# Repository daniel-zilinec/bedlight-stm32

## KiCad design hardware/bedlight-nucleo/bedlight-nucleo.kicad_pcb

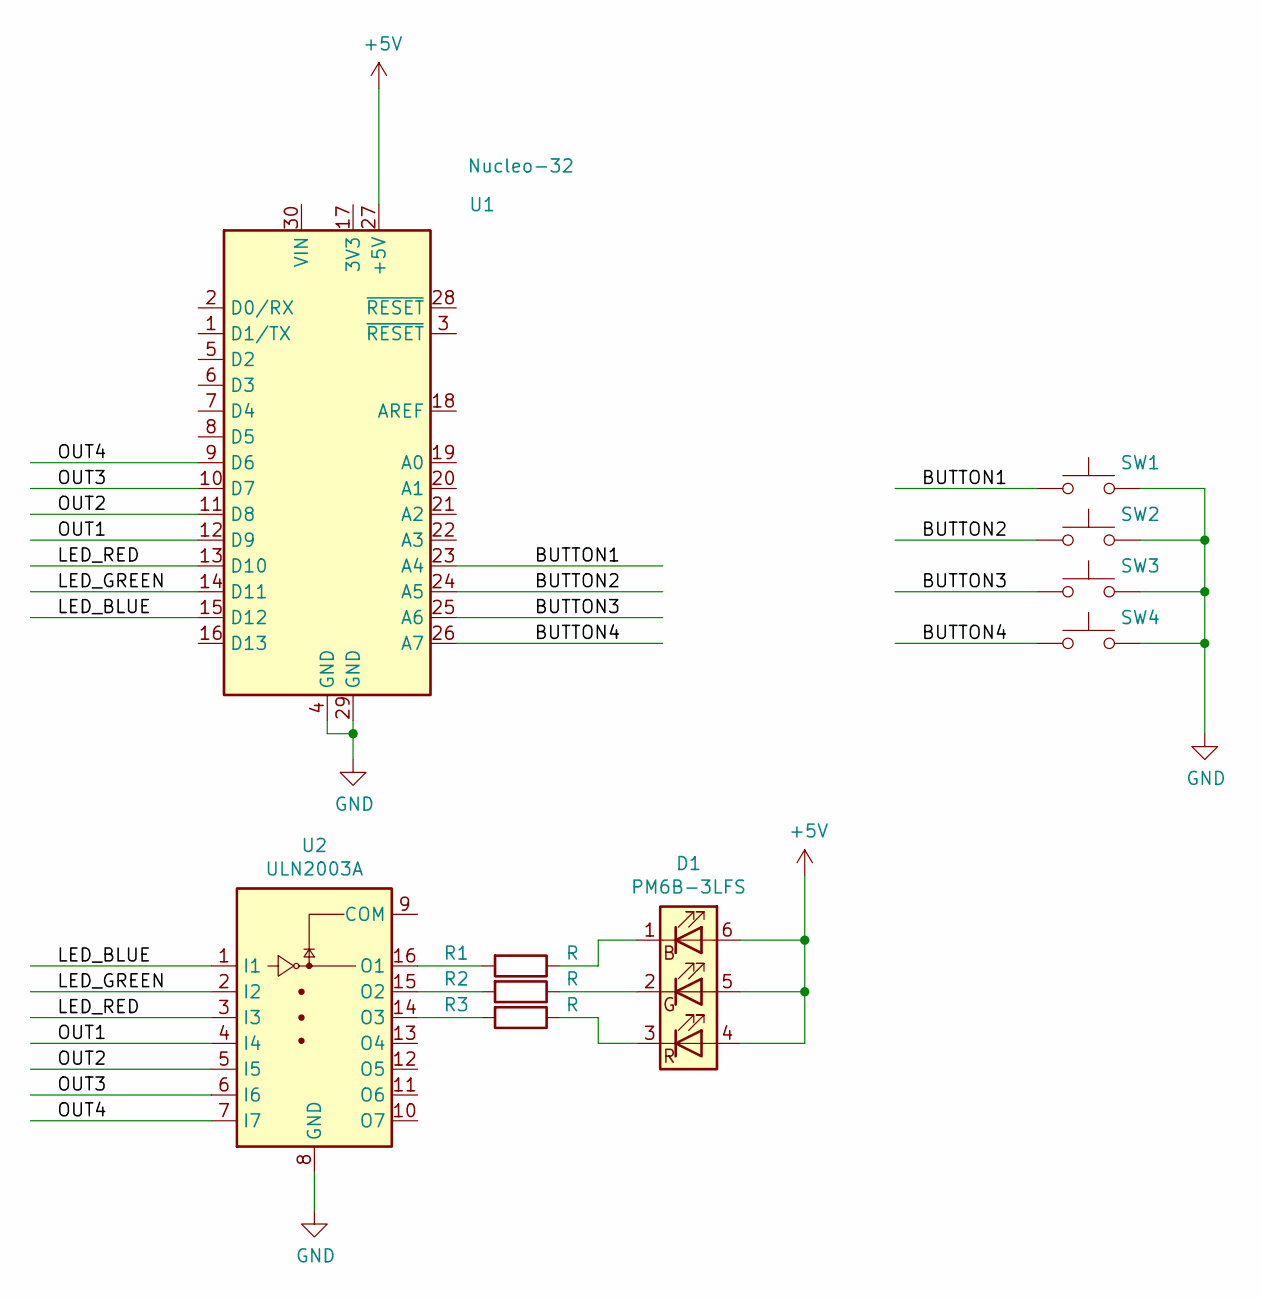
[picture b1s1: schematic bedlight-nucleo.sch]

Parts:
D1: PM6B-3LFS
R1, R2, R3: R; R_Axial_DIN0207_L6.3mm_D2.5mm_P10.16mm_Horizontal
SW1, SW2, SW3, SW4: SW_Push; SW_Push_1P1T_NO_CK_KSC6xxJ
U1: Nucleo-32
U2: ULN2003A; DIP-16_W7.62mm

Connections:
+5V: D1.4 (BA), D1.5 (GA), D1.6 (RA), U1.27 (+5V)
/BUTTON1: SW1.1, U1.23 (A4)
/BUTTON2: SW2.1, U1.24 (A5)
/BUTTON3: SW3.1, U1.25 (A6)
/BUTTON4: SW4.1, U1.26 (A7)
/LED_BLUE: U1.15 (D12), U2.1 (I1)
/LED_GREEN: U1.14 (D11), U2.2 (I2)
/LED_RED: U1.13 (D10), U2.3 (I3)
/OUT1: U1.12 (D9), U2.4 (I4)
/OUT2: U1.11 (D8), U2.5 (I5)
/OUT3: U1.10 (D7), U2.6 (I6)
/OUT4: U1.9 (D6), U2.7 (I7)
GND: SW1.2, SW2.2, SW3.2, SW4.2, U1.4 (GND), U1.29 (GND), U2.8 (GND)
unnamed: D1.1 (RK), R1.1
unnamed: D1.2 (GK), R2.1
unnamed: D1.3 (BK), R3.1
unnamed: R1.2, U2.16 (O1)
unnamed: R2.2, U2.15 (O2)
unnamed: R3.2, U2.14 (O3)

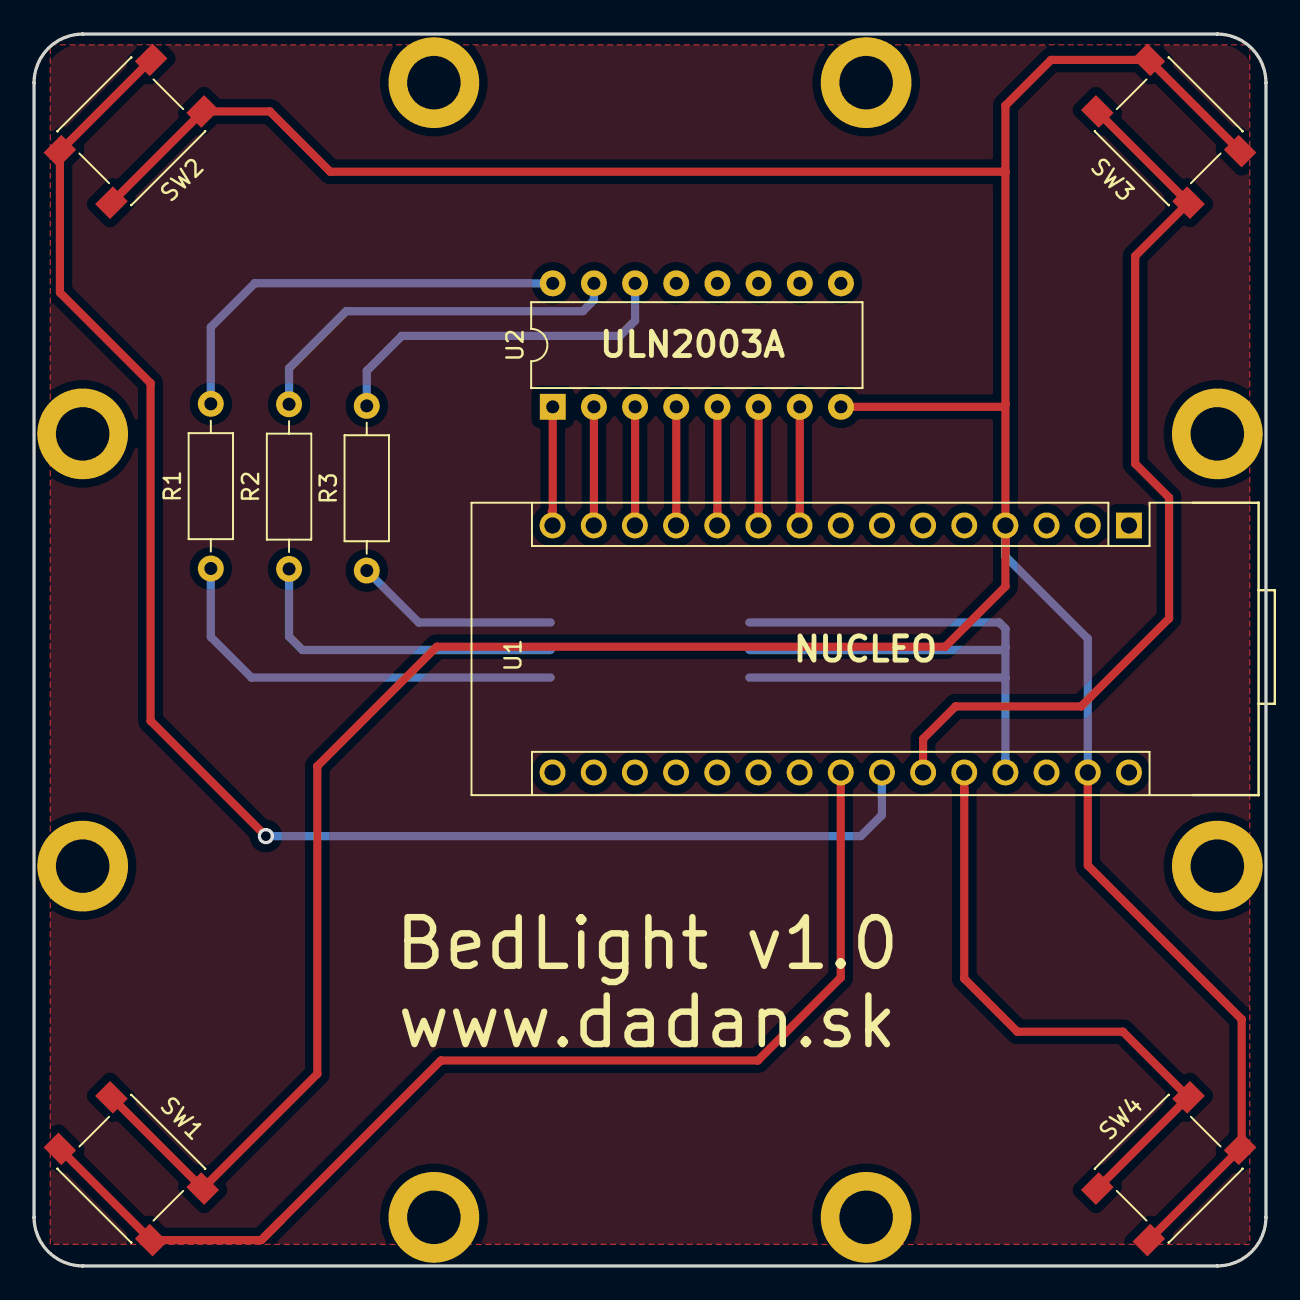
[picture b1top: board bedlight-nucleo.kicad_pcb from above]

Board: 2 copper layers, 76.0 x 76.0 mm, 18 parts (1 on the bottom side), 19 nets.

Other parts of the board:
H1, H2, H3, H4, H5, H6, H7, H8: MountingHole; MountingHole_3.2mm_M3_DIN965_Pad

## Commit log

2020-07-11 Schematic done, ready for routing
2020-07-15 Footprints partially placed
2020-07-19 Routed
2020-07-19 Added mounting holes
2020-07-19 Planes remake
2020-07-22 Generated gerbers
2020-10-18 Button footprints changed - ready for production
    * Screw holes 3,2mm -> 3,3 mm
    * Changed button footprint
    * Enlarged copper fill on both sides
2020-10-18 Removed gerbers
2020-10-18 Unsaved changes from previous commit
2020-11-03 Resistor value set to 47R
